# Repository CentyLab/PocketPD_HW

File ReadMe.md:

Shield: [![CC BY-SA 4.0][cc-by-sa-shield]][cc-by-sa]

This work is licensed under a
[Creative Commons Attribution-ShareAlike 4.0 International License][cc-by-sa].

[![CC BY-SA 4.0][cc-by-sa-image]][cc-by-sa]

[cc-by-sa]: http://creativecommons.org/licenses/by-sa/4.0/
[cc-by-sa-image]: https://licensebuttons.net/l/by-sa/4.0/88x31.png
[cc-by-sa-shield]: https://img.shields.io/badge/License-CC%20BY--SA%204.0-lightgrey.svg

# Quick links
- PocketPD's Firmware - [GitHub](https://github.com/CentyLab/PocketPD)
- PocketPD's Project Page - [Hackaday.io](https://hackaday.io/project/194295-pocketpd-usb-c-portable-bench-power-supply)
- CentyLab website - [CentyLab.com](https://centylab.com)
- CrowdSupply Page - [CrowdSupply.com](https://www.crowdsupply.com/centylab/pocketpd)

# Hardware Overview
- Design Files - .kicad_*
	- KiCad design files
- Gerber files - _Gerber.zip; _Gerber.pdf
    - PCB copper and drill file for fabrication
- Schematic file - _Schematic.pdf
    - Schematic in PDF format
- BOMs - _bom.cvs
    - Bill of material for the PCBA and also the unit assembly for additional parts
- 3Ds files
    - Model ready for 3D printing for housing and encoder knob. You can view the models online directly on GitHub. Else, check out free online viewer [3dviewer.net](https://3dviewer.net/)
	- 3D model for the whole PocketPD PCB and Connector if you would like to model your own case.

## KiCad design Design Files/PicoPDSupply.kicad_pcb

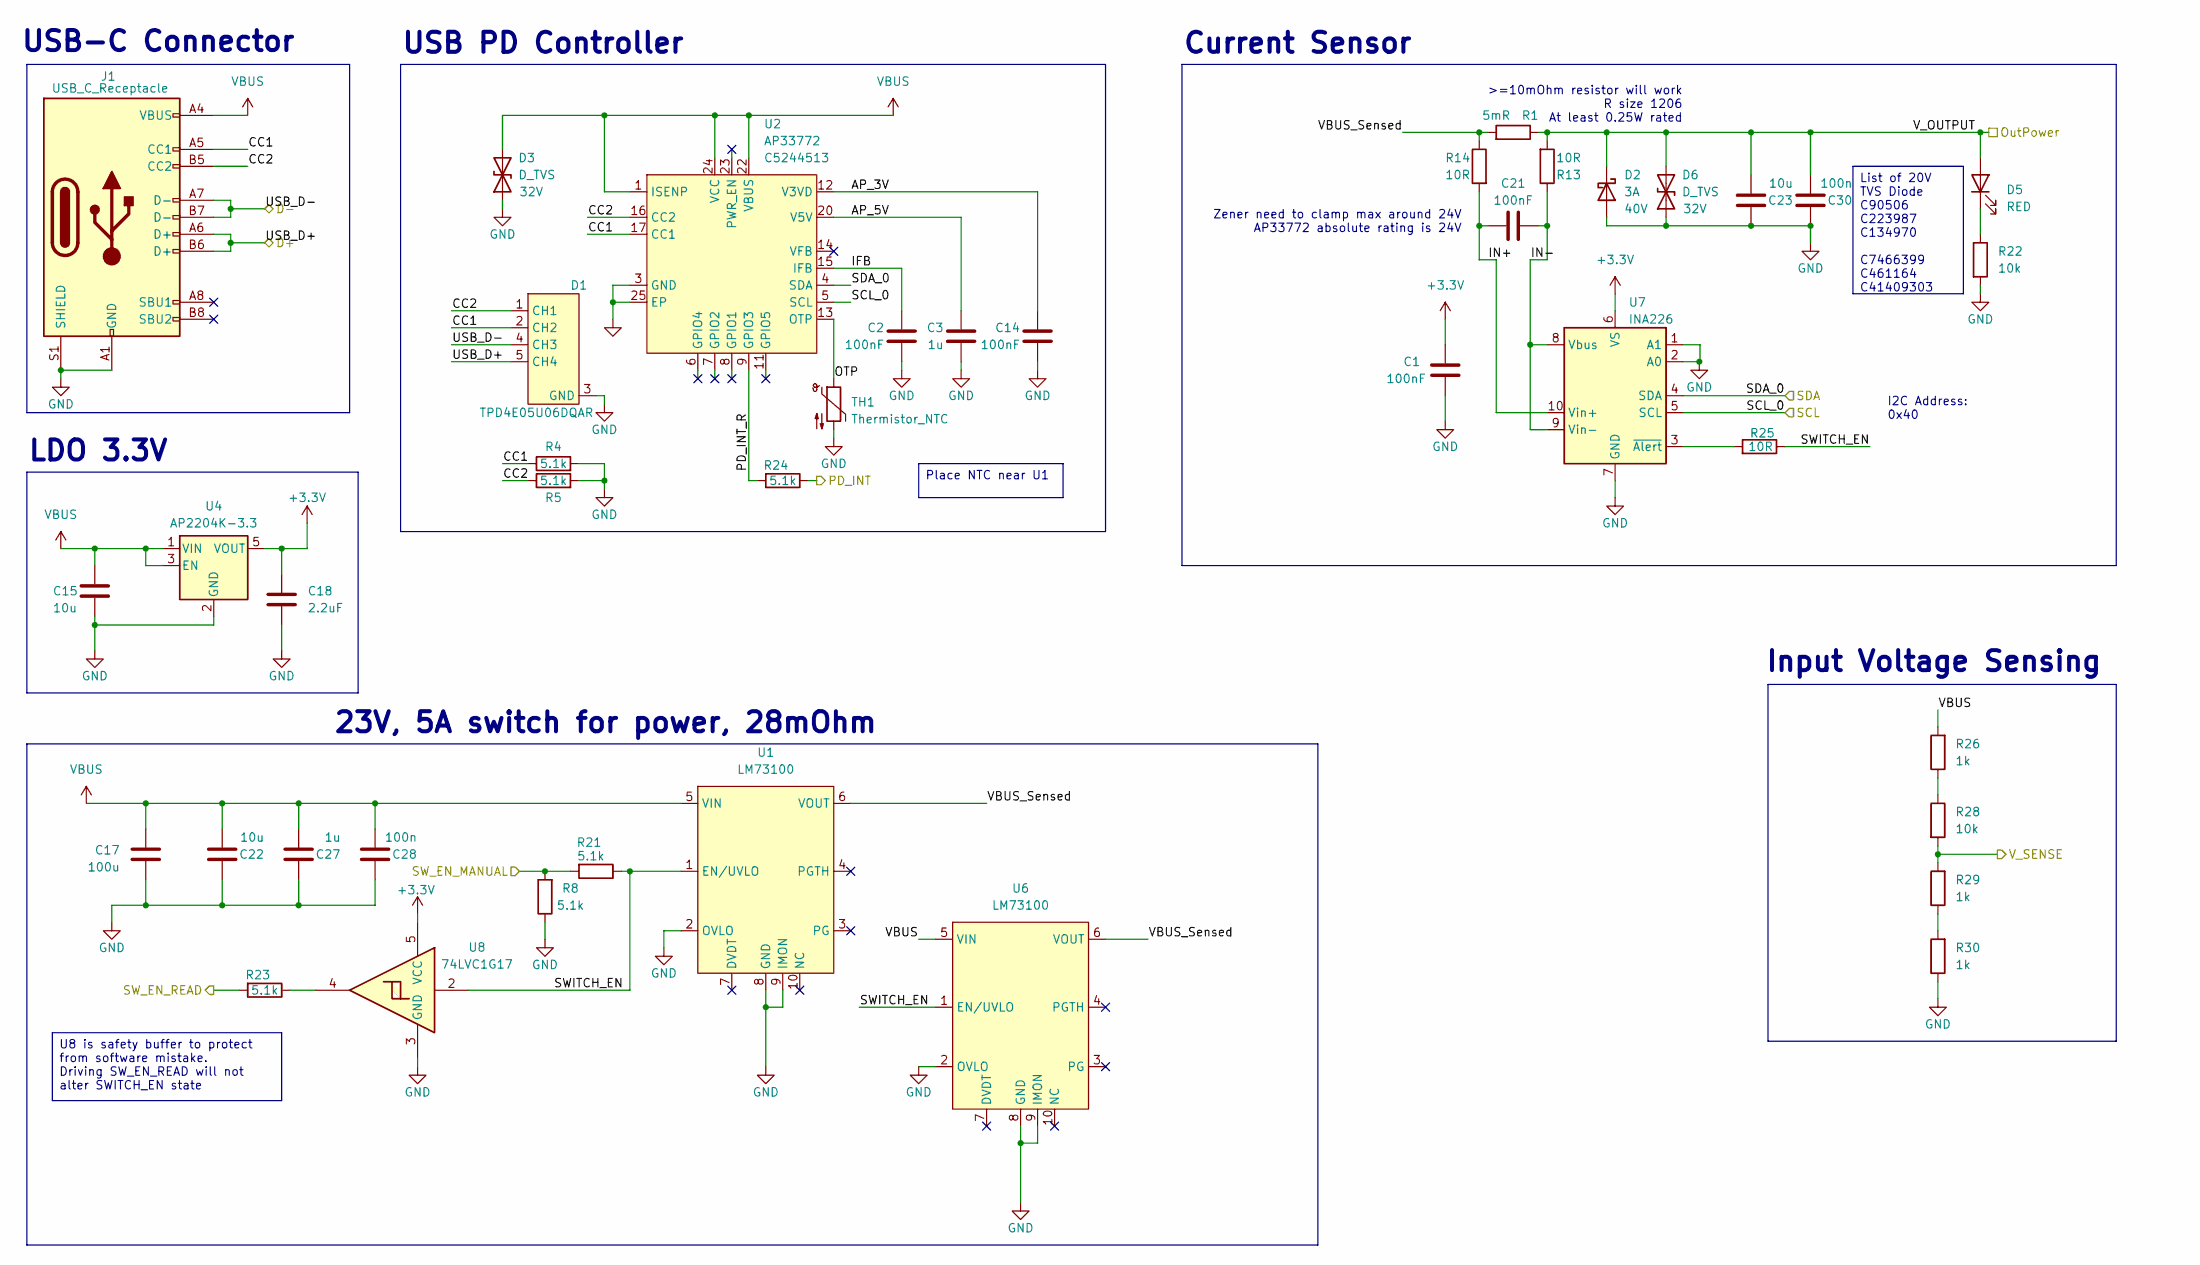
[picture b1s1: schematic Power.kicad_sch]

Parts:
C1, C2, C14, C21: 100nF; C_0402_1005Metric; LCSC C1525
C3, C27: 1u; C_0805_2012Metric; LCSC C28323
C15, C22, C23: 10u; C_1210_3225Metric; LCSC C138687
C17: 100u; CP_Elec_6.3x7.7; Manufacture # EEEFK1V101XP; LCSC C178560
C18: 2.2uF; C_0402_1005Metric; LCSC C12530
C28, C30: 100n; C_0603_1608Metric; LCSC C14663
D1: TPD4E05U06DQAR; SON50P100X255X50-10N; LCSCAlternative1 C478014
D2: D_Schottky; D_SMA; Voltage 40V; LCSC C8678
D3, D6: D_TVS; D_SMA; Clamp Voltage 32V; LCSC C19077540
D5: RED; LED_0603_1608Metric; LCSC C2286
J1: USB_C_Receptacle; USB_C_GSwitch; LCSC C963411
R1: 5mR; R_1206_3216Metric; LCSC C2988648
R4, R5, R8, R21, R23, R24: 5.1k; R_0402_1005Metric; LCSC C25905
R13, R14, R25: 10R; R_0402_1005Metric; LCSC C25077
R22, R28: 10k; R_0402_1005Metric; LCSC C25744
R26, R29, R30: 1k; R_0402_1005Metric; LCSC C11702
TH1: Thermistor_NTC; R_0402_1005Metric; LCSC C77131
U1, U6: LM73100; VQFN-HR-16; LCSC C3210761
U2: AP33772; QFN-24-1EP_4x4mm_P0.5mm_EP2.6x2.6mm; LCSC C5244513
U4: AP2204K-3.3; SOT-23-5; JLCPCB Rotation Offset 180
U7: INA226; VSSOP-10_3x3mm_P0.5mm; LCSC C49851
U8: 74LVC1G17; SOT-353_SC-70-5; LCSC C10425

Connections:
+3.3V: C1.1, C18.1, U4.5 (VOUT), U7.6 (VS), U8.5 (VCC); also elsewhere on the board
/Connection/V_OUTPUT: C23.2, C30.2, D2.1 (K), D5.2 (A), D6.2 (A2), R1.1, R13.2; also elsewhere on the board
/MicroController/ADC3: R28.2, R29.2; also elsewhere on the board
/MicroController/GPIO1: R8.2, R21.2; also elsewhere on the board
/MicroController/GPIO2: R23.2; also elsewhere on the board
/MicroController/GPIO24: R24.1; also elsewhere on the board
/MicroController/USB_D+: D1.5 (CH4), D1.6, J1.A6 (D+), J1.B6 (D+); also elsewhere on the board
/MicroController/USB_D-: D1.4 (CH3), D1.7, J1.A7 (D-), J1.B7 (D-); also elsewhere on the board
/Power/AP_3V: C14.1, U2.12 (V3VD)
/Power/AP_5V: C3.1, U2.20 (V5V)
/Power/CC1: D1.2 (CH2), D1.9, J1.A5 (CC1), R4.1, U2.17 (CC1)
/Power/CC2: D1.1 (CH1), D1.10, J1.B5 (CC2), R5.1, U2.16 (CC2)
/Power/IFB: C2.1, U2.15 (IFB)
/Power/IN+: C21.2, R14.2, U7.10 (Vin+)
/Power/IN-: C21.1, R13.1, U7.8 (Vbus), U7.9 (Vin-)
/Power/OTP: TH1.1, U2.13 (OTP)
/Power/PD_INT_R: R24.2, U2.9 (GPIO3)
/Power/SCL_0: U2.5 (SCL), U7.5 (SCL); also elsewhere on the board
/Power/SDA_0: U2.4 (SDA), U7.4 (SDA); also elsewhere on the board
/Power/SWITCH_EN: R21.1, R25.1, U1.1 (EN/UVLO), U6.1 (EN/UVLO), U8.2
/Power/VBUS_Sensed: R1.2, R14.1, U1.6 (VOUT), U6.6 (VOUT)
GND: C1.2, C2.2, C3.2, C14.2, C15.2, C17.2, C18.2, C22.1, C23.1, C27.1, C28.1, C30.1, D1.3 (GND), D1.8 (GND), D2.2 (A), D3.1 (A1), D6.1 (A1), J1.A1 (GND), J1.A12 (GND), J1.B1 (GND), J1.B12 (GND), J1.S1 (SHIELD), R4.2, R5.2, R8.1, R22.2, R30.1, TH1.2, U1.2 (OVLO), U1.8 (GND), U1.9 (IMON), U2.3 (GND), U2.25 (EP), U4.2 (GND), U6.2 (OVLO), U6.8 (GND), U6.9 (IMON), U7.1 (A1), U7.2 (A0), U7.7 (GND), U8.3 (GND); also elsewhere on the board
unnamed: D5.1 (K), R22.1
unnamed: R23.1, U8.4
unnamed: R26.1, R28.1
unnamed: R29.1, R30.2
unnamed: R25.2, U7.3 (~Alert)
VBUS: C15.1, C17.1, C22.2, C27.2, C28.2, D3.2 (A2), J1.A4 (VBUS), J1.A9 (VBUS), J1.B4 (VBUS), J1.B9 (VBUS), R26.2, U1.5 (VIN), U2.1 (ISENP), U2.22 (VBUS), U2.24 (VCC), U4.1 (VIN), U4.3 (EN), U6.5 (VIN)

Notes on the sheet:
Input Voltage Sensing
>=10mOhm resistor will work R size 1206 At least 0.25W rated
Zener need to clamp max around 24V AP33772 absolute rating is 24V
USB-C Connector
Current Sensor
USB PD Controller
23V, 5A switch for power, 28mOhm
I2C Address: 0x40
LDO 3.3V
Place NTC near U1
List of 20V TVS Diode C90506 C223987 C134970 C7466399 C461164 C41409303
U8 is safety buffer to protect from software mistake. Driving SW_EN_READ will not alter SWITCH_EN state

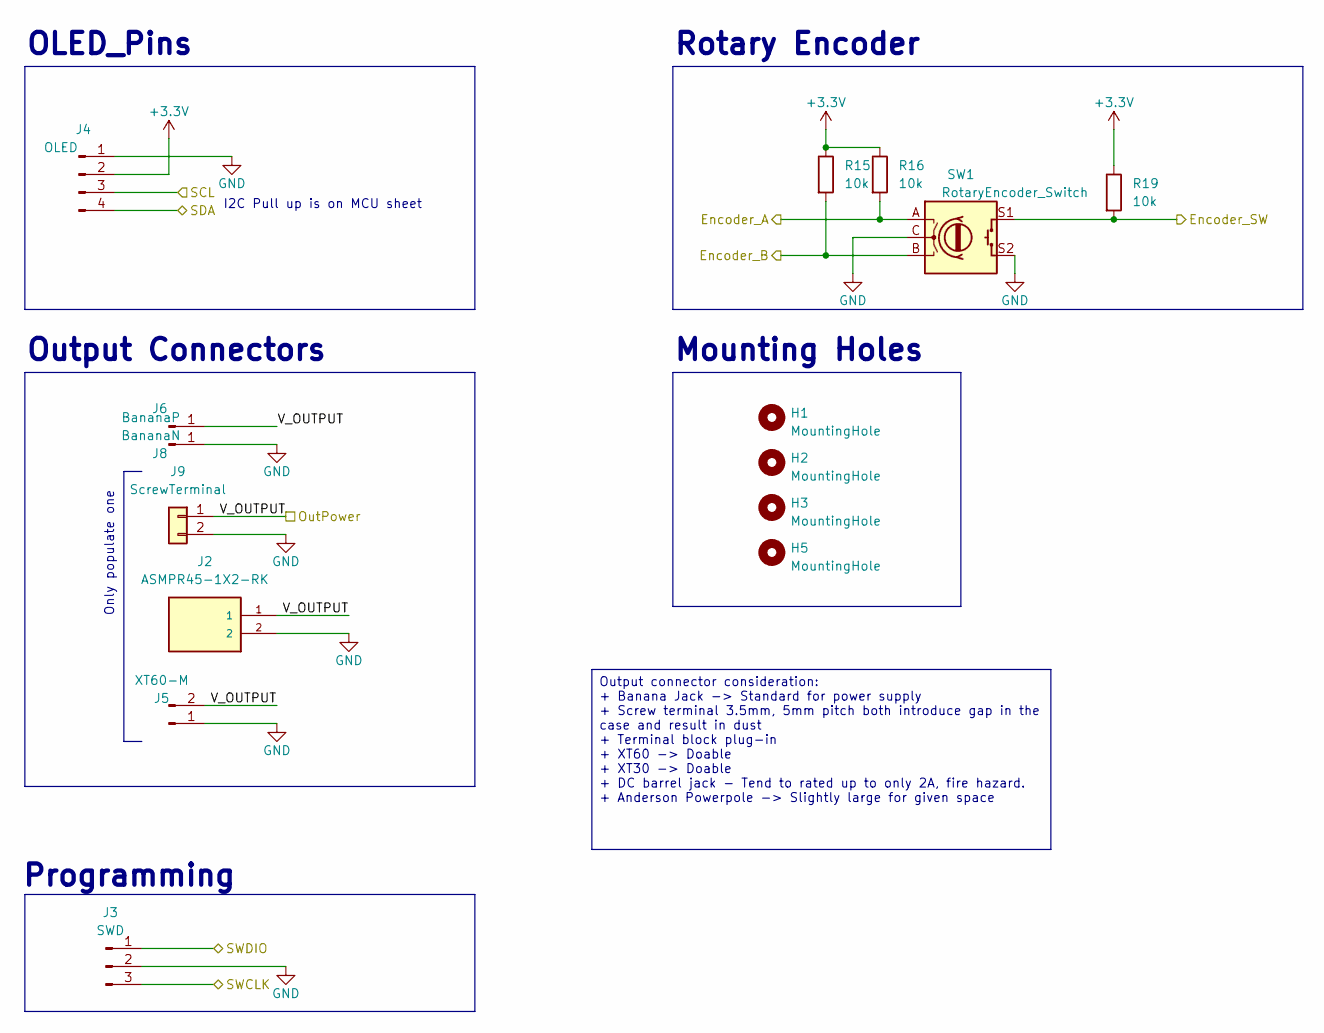
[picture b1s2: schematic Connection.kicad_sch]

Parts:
H1: MountingHole; MountingHole_2.2mm_M2_DIN965
H2, H3, H5: MountingHole; MountingHole_2.2mm_M2_DIN965_Pad
J2: ASMPR45-1X2-RK; Conn_ASMPR45-1X2-RK
J3: SWD; PinHeader_1x03_P2.54mm_Vertical
J4: OLED; Conn_OLED_PocketPD; LCSC C20071191
J5: XT60-M; AMASS_XT60PW-M_1x02_P7.20mm_Horizontal
J6: BananaP; Banana_Cliff_FCR7350R_S16N-PC_Horizontal; LCSC C7437326
J8: BananaN; Banana_Cliff_FCR7350B_S16N-PC_Horizontal; LCSC C7437327
J9: ScrewTerminal; PhoenixContact_MC_1,5_2-G-3.81_1x02_P3.81mm_Horizontal; LCSC C5259145
R15, R16, R19: 10k; R_0402_1005Metric; LCSC C25744
SW1: RotaryEncoder_Switch; RotaryEncoder_EC11B_SW_Horizontal; LCSC C9900176956

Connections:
+3.3V: J4.2, R15.1, R16.1, R19.1; also elsewhere on the board
/Connection/V_OUTPUT: J2.1, J5.2, J6.1, J9.1; also elsewhere on the board
/MicroController/GPIO18: R19.2, SW1.S1; also elsewhere on the board
/MicroController/GPIO19: R16.2, SW1.A; also elsewhere on the board
/MicroController/GPIO20: R15.2, SW1.B; also elsewhere on the board
/MicroController/SWCLK: J3.3; also elsewhere on the board
/MicroController/SWDIO: J3.1; also elsewhere on the board
/Power/SCL_0: J4.3; also elsewhere on the board
/Power/SDA_0: J4.4; also elsewhere on the board
GND: J2.2, J3.2, J4.1, J5.1, J8.1, J9.2, SW1.C, SW1.S2; also elsewhere on the board

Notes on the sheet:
Only populate one
Mounting Holes
Output Connectors
Rotary Encoder
OLED_Pins
Programming
I2C Pull up is on MCU sheet
Output connector consideration: + Banana Jack -> Standard for power supply + Screw terminal 3.5mm, 5mm pitch both introduce gap in the case and result in dust + Terminal block plug-in + XT60 -> Doable + XT30 -> Doable + DC barrel jack - Tend to rated up to only 2A, fire hazard. + Anderson Powerpole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

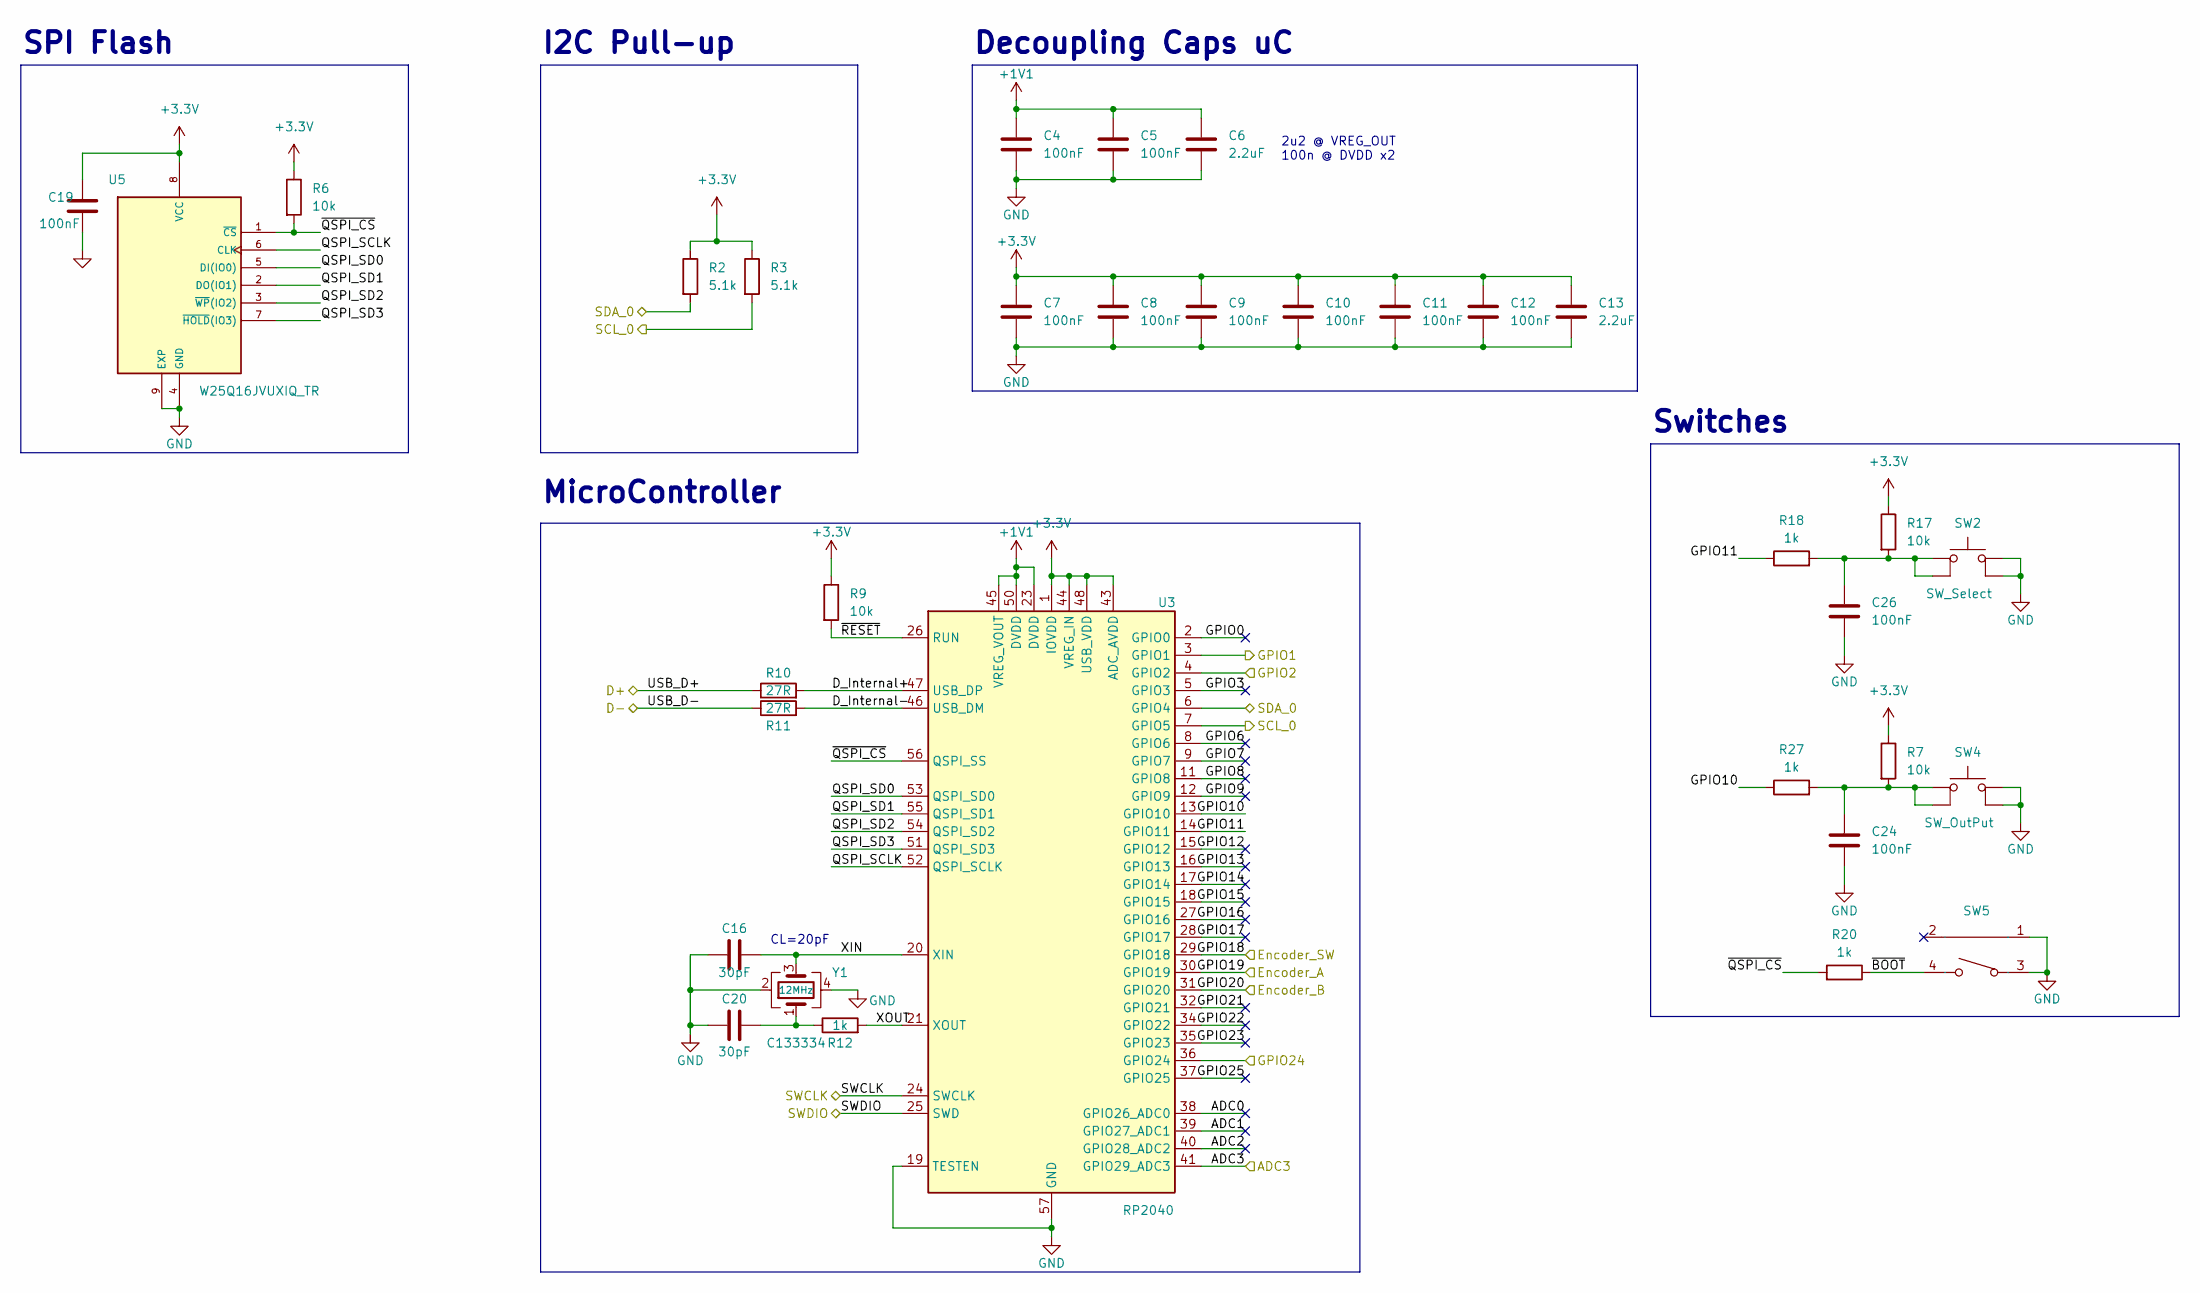
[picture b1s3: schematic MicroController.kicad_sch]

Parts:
C4, C5, C7, C8, C9, C10, C11, C12, C19, C24, C26: 100nF; C_0402_1005Metric; LCSC C1525
C6, C13: 2.2uF; C_0402_1005Metric; LCSC C12530
C16, C20: 30pF; C_0402_1005Metric; LCSC C1570
R2, R3: 5.1k; R_0402_1005Metric; LCSC C25905
R6, R7, R9, R17: 10k; R_0402_1005Metric; LCSC C25744
R10, R11: 27R; R_0402_1005Metric; LCSC C138021
R12, R18, R20, R27: 1k; R_0402_1005Metric; LCSC C11702
SW2: SW_Select; Button_6.2x6.2x12mm; LCSC C2762973
SW4: SW_OutPut; Button_6.2x6.2x12mm; LCSC C2762973
SW5: Button-SMD_TS24CA; LCSC C692458
U3: RP2040; QFN-56-1EP_7x7mm_P0.4mm_EP3.2x3.2mm; LCSC C2040
U5: W25Q16JVUXIQ_TR; 8-USON; PARTREV H; LCSC C2843335
Y1: 12MHz; Crystal_SMD_3225-4Pin_3.2x2.5mm; LCSC C133334

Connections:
+1V1: C4.1, C5.1, C6.1, U3.23 (DVDD), U3.45 (VREG_VOUT), U3.50 (DVDD)
+3.3V: C7.1, C8.1, C9.1, C10.1, C11.1, C12.1, C13.1, C19.1, R2.1, R3.1, R6.1, R7.1, R9.1, R17.1, U3.1 (IOVDD), U3.10 (IOVDD), U3.22 (IOVDD), U3.33 (IOVDD), U3.42 (IOVDD), U3.43 (ADC_AVDD), U3.44 (VREG_IN), U3.48 (USB_VDD), U3.49 (IOVDD), U5.8 (VCC); also elsewhere on the board
/MicroController/ADC0: U3.38 (GPIO26_ADC0)
/MicroController/ADC1: U3.39 (GPIO27_ADC1)
/MicroController/ADC2: U3.40 (GPIO28_ADC2)
/MicroController/ADC3: U3.41 (GPIO29_ADC3); also elsewhere on the board
/MicroController/D_Internal+: R10.2, U3.47 (USB_DP)
/MicroController/D_Internal-: R11.2, U3.46 (USB_DM)
/MicroController/GPIO0: U3.2 (GPIO0)
/MicroController/GPIO1: U3.3 (GPIO1); also elsewhere on the board
/MicroController/GPIO2: U3.4 (GPIO2); also elsewhere on the board
/MicroController/GPIO3: U3.5 (GPIO3)
/MicroController/GPIO6: U3.8 (GPIO6)
/MicroController/GPIO7: U3.9 (GPIO7)
/MicroController/GPIO8: U3.11 (GPIO8)
/MicroController/GPIO9: U3.12 (GPIO9)
/MicroController/GPIO10: R27.1, U3.13 (GPIO10)
/MicroController/GPIO11: R18.1, U3.14 (GPIO11)
/MicroController/GPIO12: U3.15 (GPIO12)
/MicroController/GPIO13: U3.16 (GPIO13)
/MicroController/GPIO14: U3.17 (GPIO14)
/MicroController/GPIO15: U3.18 (GPIO15)
/MicroController/GPIO16: U3.27 (GPIO16)
/MicroController/GPIO17: U3.28 (GPIO17)
/MicroController/GPIO18: U3.29 (GPIO18); also elsewhere on the board
/MicroController/GPIO19: U3.30 (GPIO19); also elsewhere on the board
/MicroController/GPIO20: U3.31 (GPIO20); also elsewhere on the board
/MicroController/GPIO21: U3.32 (GPIO21)
/MicroController/GPIO22: U3.34 (GPIO22)
/MicroController/GPIO23: U3.35 (GPIO23)
/MicroController/GPIO24: U3.36 (GPIO24); also elsewhere on the board
/MicroController/GPIO25: U3.37 (GPIO25)
/MicroController/QSPI_SCLK: U3.52 (QSPI_SCLK), U5.6 (CLK)
/MicroController/QSPI_SD0: U3.53 (QSPI_SD0), U5.5 (DI(IO0))
/MicroController/QSPI_SD1: U3.55 (QSPI_SD1), U5.2 (DO(IO1))
/MicroController/QSPI_SD2: U3.54 (QSPI_SD2), U5.3 (~WP(IO2))
/MicroController/QSPI_SD3: U3.51 (QSPI_SD3), U5.7 (~HOLD(IO3))
/MicroController/SWCLK: U3.24 (SWCLK); also elsewhere on the board
/MicroController/SWDIO: U3.25 (SWD); also elsewhere on the board
/MicroController/USB_D+: R10.1; also elsewhere on the board
/MicroController/USB_D-: R11.1; also elsewhere on the board
/MicroController/XIN: C16.1, U3.20 (XIN), Y1.3
/MicroController/XOUT: R12.2, U3.21 (XOUT)
/MicroController/~BOOT: R20.1, SW5.4
/MicroController/~QSPI_CS: R6.2, R20.2, U3.56 (QSPI_SS), U5.1 (~CS)
/MicroController/~RESET: R9.2, U3.26 (RUN)
/Power/SCL_0: R3.2, U3.7 (GPIO5); also elsewhere on the board
/Power/SDA_0: R2.2, U3.6 (GPIO4); also elsewhere on the board
GND: C4.2, C5.2, C6.2, C7.2, C8.2, C9.2, C10.2, C11.2, C12.2, C13.2, C16.2, C19.2, C20.2, C24.2, C26.2, SW2.3 (B), SW2.4 (A), SW4.3 (B), SW4.4 (A), SW5.1, SW5.3, U3.19 (TESTEN), U3.57 (GND), U5.4 (GND), U5.9 (EXP), Y1.2, Y1.4; also elsewhere on the board
unnamed: C20.1, R12.1, Y1.1
unnamed: C24.1, R7.2, R27.2, SW4.1 (A), SW4.2 (A)
unnamed: C26.1, R17.2, R18.2, SW2.1 (A), SW2.2 (A)

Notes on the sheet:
Decoupling Caps uC
I2C Pull-up
SPI Flash
MicroController
CL=20pF
Switches
2u2 @ VREG_OUT 100n @ DVDD x2

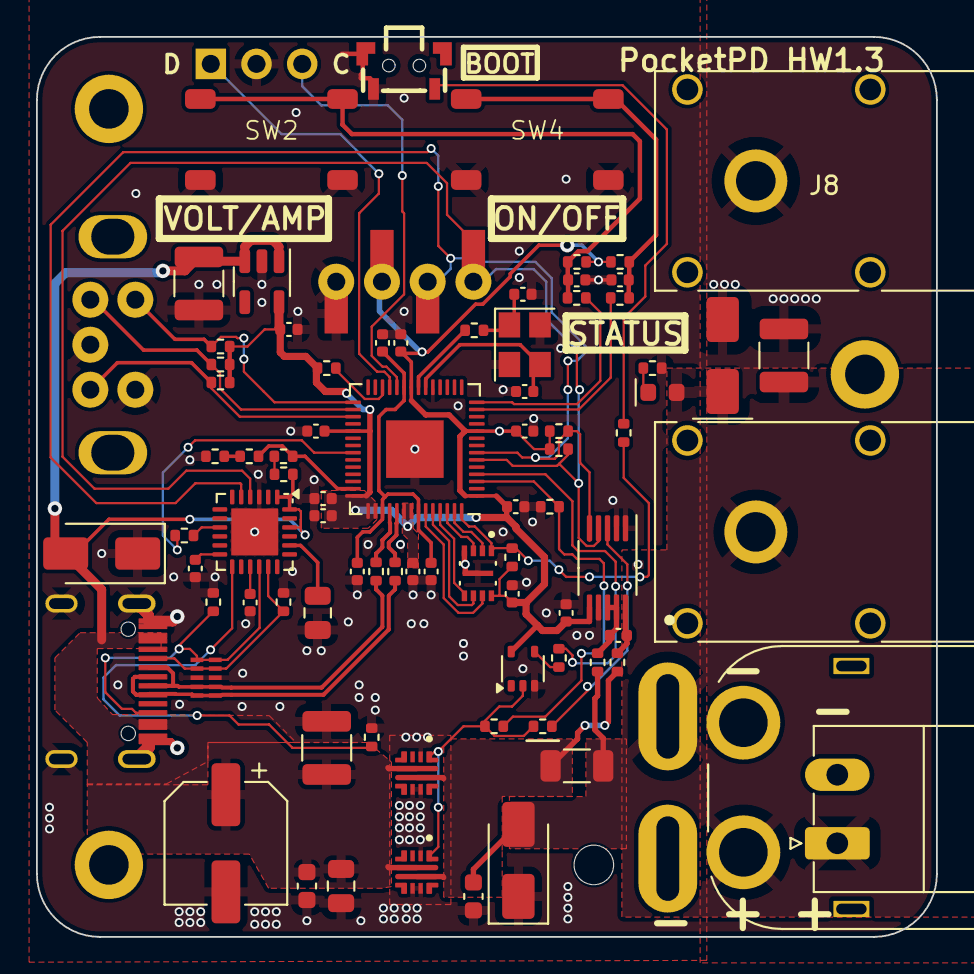
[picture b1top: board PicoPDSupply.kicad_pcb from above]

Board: 2 copper layers, 50.0 x 50.0 mm, 89 parts (0 on the bottom side), 51 nets.

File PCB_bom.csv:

Designator,Footprint,Quantity,Value,LCSC Part #
"C1, C10, C11, C12, C14, C19, C2, C21, C24, C26, C4, C5, C7, C8, C9",402,15,100nF,C1525
"C13, C18, C6",402,3,2.2uF,C12530
"C15, C22, C23",1210,3,10u,C138687
"C16, C20",402,2,30pF,C1570
C17,CP_Elec_6.3x7.7,1,100u,C178560
"C27, C3",805,2,1u,C28323
"C28, C30",603,2,100n,C14663
D1,SON50P100X255X50-10N,1,TPD4E05U06DQAR,C138714
D2,D_SMA,1,D_Schottky,C8678
"D3, D6",D_SMA,2,D_TVS,C19077540
D5,603,1,RED,C2286
J1,USB_C,1,USB_C_Receptacle,C963411
J4,Conn_OLED_PocketPD,1,OLED,C20071191
J6,Banana_Cliff_FCR7350R_S16N-PC_Horizontal,1,BananaP,C7437326
J8,Banana_Cliff_FCR7350B_S16N-PC_Horizontal,1,BananaN,C7437327
R1,1206,1,5mR,C2988648
"R10, R11",402,2,27R,C138021
"R12, R18, R20, R26, R27, R29, R30",402,7,1k,C11702
"R13, R14, R25",402,3,10R,C25077
"R15, R16, R17, R19, R22, R28, R6, R7, R9",402,9,10k,C25744
"R2, R21, R23, R24, R3, R4, R5, R8",402,8,5.1k,C25905
SW1,RotaryEncoder_EC11B_SW_Horizontal,1,RotaryEncoder_Switch,
SW2,Button_6.2x6.2x12mm,1,SW_Select,C2762973
SW4,Button_6.2x6.2x12mm,1,SW_OutPut,C2762973
SW5,Button-SMD_TS24CA,1,SW_Boot,C692458
TH1,402,1,Thermistor_NTC,C77131
"U1, U6",VQFN-HR-16,2,LM73100,C3210761
U2,QFN-24-1EP_4x4mm_P0.5mm_EP2.6x2.6mm,1,AP33772,C5244513
U3,QFN-56-1EP_7x7mm_P0.4mm_EP3.2x3.2mm,1,RP2040,C2040
U4,SOT-23-5,1,AP2204K-3.3,C112032
U5,8-USON,1,W25Q16JVUXIQ_TR,C2843335
U7,VSSOP-10_3x3mm_P0.5mm,1,INA226,C49851
U8,SOT-353_SC-70-5,1,74LVC1G17,C10425
Y1,Crystal_SMD_3225-4Pin_3.2x2.5mm,1,12MHz,C133334

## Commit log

2025-06-29 Update 3D bottom, add 3D knob
    New 3D bottom has 0.4mm layer height for magnet area. Ensure easier printing.
2025-09-15 Added Readme
2025-11-22 Push HW1.2
2025-11-22 Push HW1.3
2026-01-02 Add KiCad files
2026-01-03 Add license
